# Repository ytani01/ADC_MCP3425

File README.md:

# ADC_MCP3425

MCP3425 ADC librariy for Python3 on Raspberry Pi

## 

## A. References

* [pigpio](https://abyz.me.uk/rpi/pigpio/python.html)

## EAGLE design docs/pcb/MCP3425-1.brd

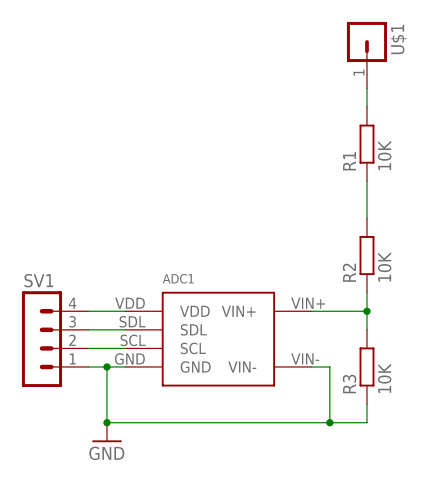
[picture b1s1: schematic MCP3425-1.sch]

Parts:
ADC1: MCP3425MOD
R1, R2, R3: 10K; 0204/5
SV1: PINHEAD-MA04-1
U$1: PINHEAD-MA01-1

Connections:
GND: ADC1.GND, ADC1.VIN-, R3.1, SV1.1
unnamed: ADC1.VDD, SV1.4
unnamed: ADC1.SDL, SV1.3
unnamed: ADC1.SCL, SV1.2
unnamed: R1.2, U$1.1
unnamed: ADC1.VIN+, R2.1, R3.2
unnamed: R1.1, R2.2

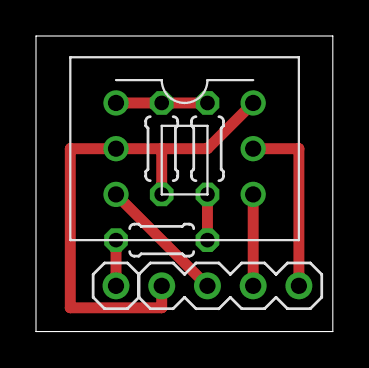
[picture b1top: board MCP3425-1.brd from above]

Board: 2 copper layers, 16.5 x 16.4 mm, 6 parts (0 on the bottom side), 7 nets.

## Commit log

2020-10-01 datasheet
2021-09-27 0.0.1
2021-09-27 ADD: SensorWatcher
2021-11-01 UPD: test2.py
2021-11-13 UPD: test
2021-11-13 ADD: v_mon.sh wrapper.sh
2021-11-13 FIX: v_mon.sh
